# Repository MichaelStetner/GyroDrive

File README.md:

# GyroDrive
Motorized microdrive with integrated gyroscope, accelerometer, and compass

## Connector
The connector is a 7-pin male nano dual row connector from Omnetics (part number A75243-001).

Here is the pinout solder pads, as viewed from above with the connector pins pointing up

```
|                                                                       |
|                              Connector                                |
|                                Body                                   |
|                                                                       |
|                                                                       |
|-----------------------------------------------------------------------|

  |------|  |------|  |------|  |------|  |------|  |------|  |------|
  |      |  |      |  |      |  |      |  |      |  |      |  |      |
  | SCL  |  | SDA  |  |  S1  |  |  S2  |  | +VS  |  | -VS  |  | STIM |
  |      |  |      |  |      |  |      |  |      |  |      |  | OUT  |
  |      |  |      |  |      |  |      |  |      |  |      |  |      |
  |------|  |------|  |------|  |------|  |------|  |------|  |------|

  |------|  |------|  |------|  |------|  |------|  |------|  |------|
  |      |  |      |  |      |  |      |  |      |  |      |  |      |
  | DGND |  |  IX  |  |  S3  |  |  S4  |  | ICOM |  | AGND |  | STIM |
  |      |  |      |  |      |  |      |  |      |  |      |  |  IN  |
  |      |  |      |  |      |  |      |  |      |  |      |  |      |
  |------|  |------|  |------|  |------|  |------|  |------|  |------|
```

Here is the same pinout for the connector pins, as viewed looking head on into the pins with the board on the bottom

```
   /                                                                /
  /                                                                /
 /                                                                /
|----------------------------------------------------------------|
| |------| |------| |------| |------| |------| |------| |------| |
| | STIM | | AGND | | ICOM | |  S4  | |  S3  | |  IX  | | DGND | |
| |  IN  | |      | |      | |      | |      | |      | |      | |
| |------| |------| |------| |------| |------| |------| |------| |
|                                                                |    
| |------| |------| |------| |------| |------| |------| |------| |
| | STIM | | -VS  | | +VS  | |  S2  | |  S1  | | SDA  | | SCL  | |
| | OUT  | |      | |      | |      | |      | |      | |      | |  /
| |------| |------| |------| |------| |------| |------| |------| | /
|----------------------------------------------------------------|/
                            Board side
```

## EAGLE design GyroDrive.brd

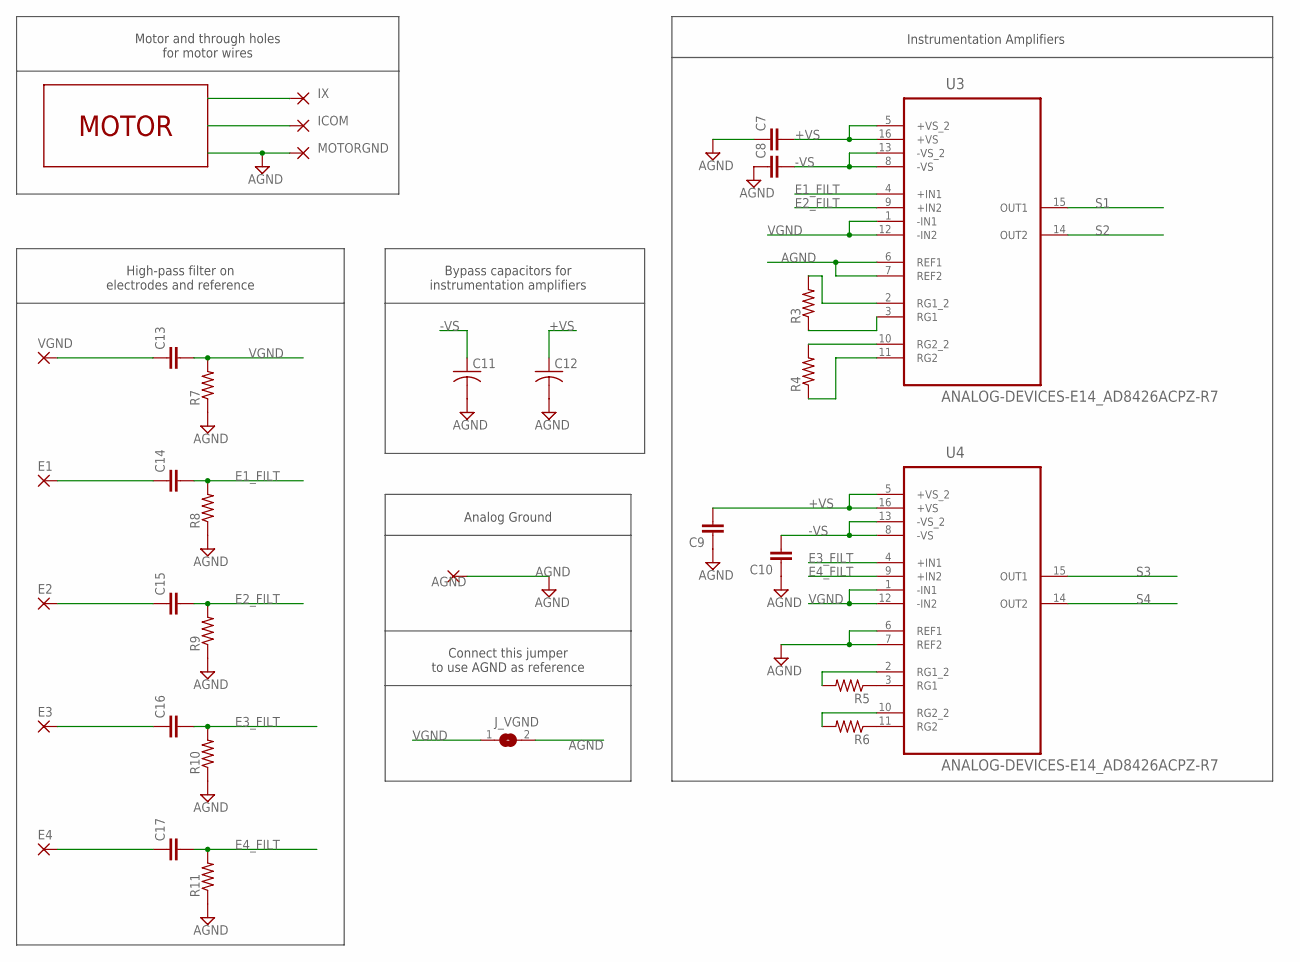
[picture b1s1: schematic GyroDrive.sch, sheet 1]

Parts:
AGND: THROUGH-HOLE-30MIL/15MIL; 30MIL/15MIL
C7, C8, C9, C10, C13, C14, C15, C16, C17: C-EUC0201; C0201
C11, C12: C-USC0603; C0603
E1, E2, E3, E4: SMD25-25-MIL
ICOM: THROUGH-HOLE-30MIL/15MIL; 30MIL/15MIL
IX: THROUGH-HOLE-30MIL/15MIL; 30MIL/15MIL
J_VGND: SJ
MOTORGND: THROUGH-HOLE-30MIL/15MIL; 30MIL/15MIL
R3, R4, R5, R6, R7, R8, R9, R10, R11: R-US_R0201; R0201
U3, U4: ANALOG-DEVICES-E14_AD8426ACPZ-R7; ANALOG-DEVICES-E14_QFN65P400X400X100-16N
U$2: MICRODRIVE-MOTOR; 0206A001B-021-47:1-Y2825
VGND: SMD25-25-MIL

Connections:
+VS: C7.2, C9.2, C12.1, U3.5 (+VS_2), U3.16 (+VS), U4.5 (+VS_2), U4.16 (+VS)
-VS: C8.2, C10.2, C11.1, U3.8 (-VS), U3.13 (-VS_2), U4.8 (-VS), U4.13 (-VS_2)
AGND: AGND.P$1, C7.1, C8.1, C9.1, C10.1, C11.2, C12.2, J_VGND.2, MOTORGND.P$1, R7.1, R8.1, R9.1, R10.1, R11.1, U3.6 (REF1), U3.7 (REF2), U4.6 (REF1), U4.7 (REF2)
E1: C14.1, E1.1
E1_FILT: C14.2, R8.2, U3.4 (+IN1)
E2: C15.1, E2.1
E2_FILT: C15.2, R9.2, U3.9 (+IN2)
E3: C16.1, E3.1
E3_FILT: C16.2, R10.2, U4.4 (+IN1)
E4: C17.1, E4.1
E4_FILT: C17.2, R11.2, U4.9 (+IN2)
ICOM: ICOM.P$1
IX: IX.P$1
unnamed: R4.2, U3.10 (RG2_2)
unnamed: R4.1, U3.11 (RG2)
unnamed: R3.1, U3.3 (RG1)
unnamed: R3.2, U3.2 (RG1_2)
unnamed: R5.1, U4.3 (RG1)
unnamed: R5.2, U4.2 (RG1_2)
unnamed: R6.2, U4.10 (RG2_2)
unnamed: R6.1, U4.11 (RG2)
S1: U3.15 (OUT1)
S2: U3.14 (OUT2)
S3: U4.15 (OUT1)
S4: U4.14 (OUT2)
VGND: C13.2, J_VGND.1, R7.2, U3.1 (-IN1), U3.12 (-IN2), U4.1 (-IN1), U4.12 (-IN2)
VGND_IN: C13.1

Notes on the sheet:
Bypass capacitors for instrumentation amplifiers
Connect this jumper to use AGND as reference
High-pass filter on electrodes and reference
Motor and through holes for motor wires
Analog Ground
Instrumentation Amplifiers

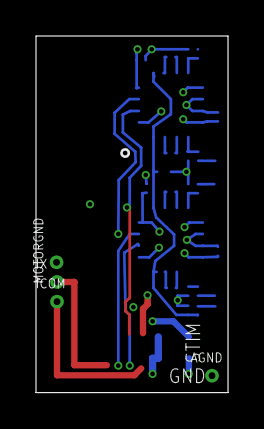
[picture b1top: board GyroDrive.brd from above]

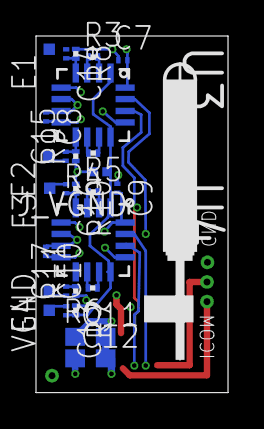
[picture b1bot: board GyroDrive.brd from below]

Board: 4 copper layers, 10.7 x 19.8 mm, 33 parts (29 on the bottom side), 20 nets.

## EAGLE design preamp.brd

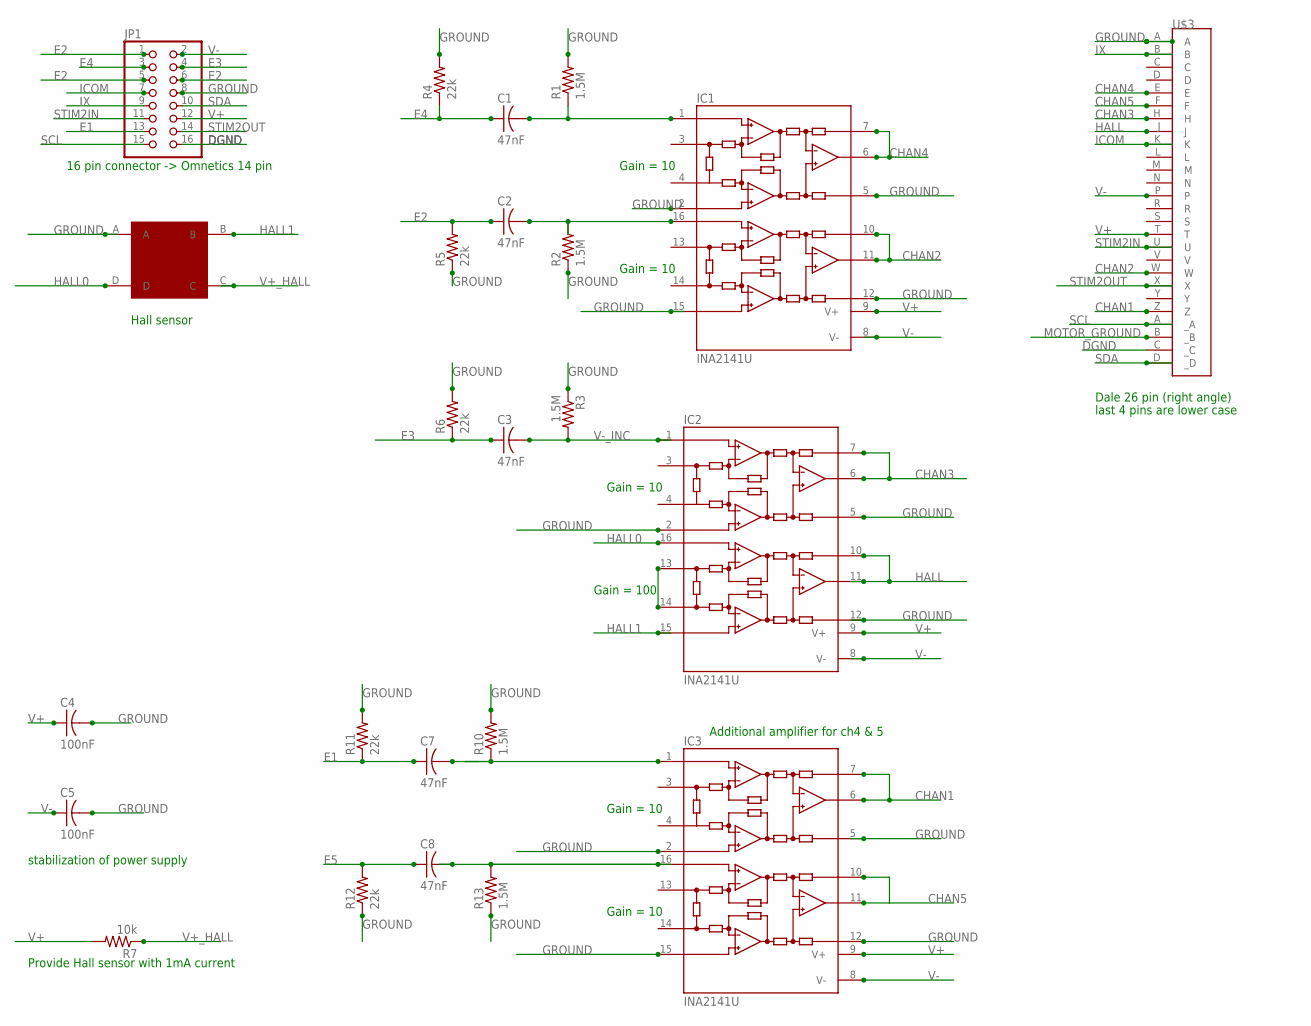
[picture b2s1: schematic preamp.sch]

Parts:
C1, C2, C3, C7, C8: 47nF; R0805ELM
C4, C5: 100nF; R0805ELM
IC1, IC2, IC3: INA2141U; SO16-1
JP1: PINHD-2X8; 2X08
R1, R2, R3, R10, R13: 1.5M; R0805ELM
R4, R5, R6, R11, R12: 22k; R0805ELM
R7: 10k; R0805ELM
U$2: HALL; HALL_ON_SIDE
U$3: MMD1P22G-26-M101

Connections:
CHAN1: IC3.6 (VOA), IC3.7 (SENSEA), U$3.Z
CHAN2: IC1.10 (SENSEB), IC1.11 (VOB), U$3.W
CHAN3: IC2.6 (VOA), IC2.7 (SENSEA), U$3.H
CHAN4: IC1.6 (VOA), IC1.7 (SENSEA), U$3.E
CHAN5: IC3.10 (SENSEB), IC3.11 (VOB), U$3.F
DGND: JP1.16, U$3._C
E1: C7.1, JP1.13, R11.1
E2: C2.1, JP1.1, JP1.5, JP1.6, R5.2
E3: C3.1, JP1.4, R6.1
E4: C1.1, JP1.3, R4.1
E5: C8.1, R12.2
GAIN_HALL: IC2.13 (JB), IC2.14 (JB)
GROUND: C4.2, C5.2, IC1.2 (INA+), IC1.5 (REFA), IC1.12 (REFB), IC1.15 (INB+), IC2.2 (INA+), IC2.5 (REFA), IC2.12 (REFB), IC3.2 (INA+), IC3.5 (REFA), IC3.12 (REFB), IC3.15 (INB+), JP1.8, R1.2, R2.1, R3.1, R4.2, R5.1, R6.2, R10.2, R11.2, R12.1, R13.1, U$2.A, U$3.A
HALL: IC2.10 (SENSEB), IC2.11 (VOB), U$3.J
HALL0: IC2.16 (INB-), U$2.D
HALL1: IC2.15 (INB+), U$2.B
ICOM: JP1.7, U$3.K
IX: JP1.9, U$3.B
MOTOR_GROUND: U$3._B
unnamed: C2.2, IC1.16 (INB-), R2.2
unnamed: C8.2, IC3.16 (INB-), R13.2
unnamed: C7.2, IC3.1 (INA-), R10.1
SCL: JP1.15, U$3._A
SDA: JP1.10, U$3._D
STIM2IN: JP1.11, U$3.U
STIM2OUT: JP1.14, U$3.X
V+: C4.1, IC1.9 (V+), IC2.9 (V+), IC3.9 (V+), JP1.12, R7.2, U$3.T
V+_HALL: R7.1, U$2.C
V-: C5.1, IC1.8 (V-), IC2.8 (V-), IC3.8 (V-), JP1.2, U$3.P
V-_INA: C1.2, IC1.1 (INA-), R1.1
V-_INC: C3.2, IC2.1 (INA-), R3.2

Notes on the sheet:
stabilization of power supply
Dale 26 pin (right angle)
Hall sensor
Additional amplifier for ch4 & 5
Gain = 100
Gain = 10
Provide Hall sensor with 1mA current
last 4 pins are lower case
16 pin connector -> Omnetics 14 pin

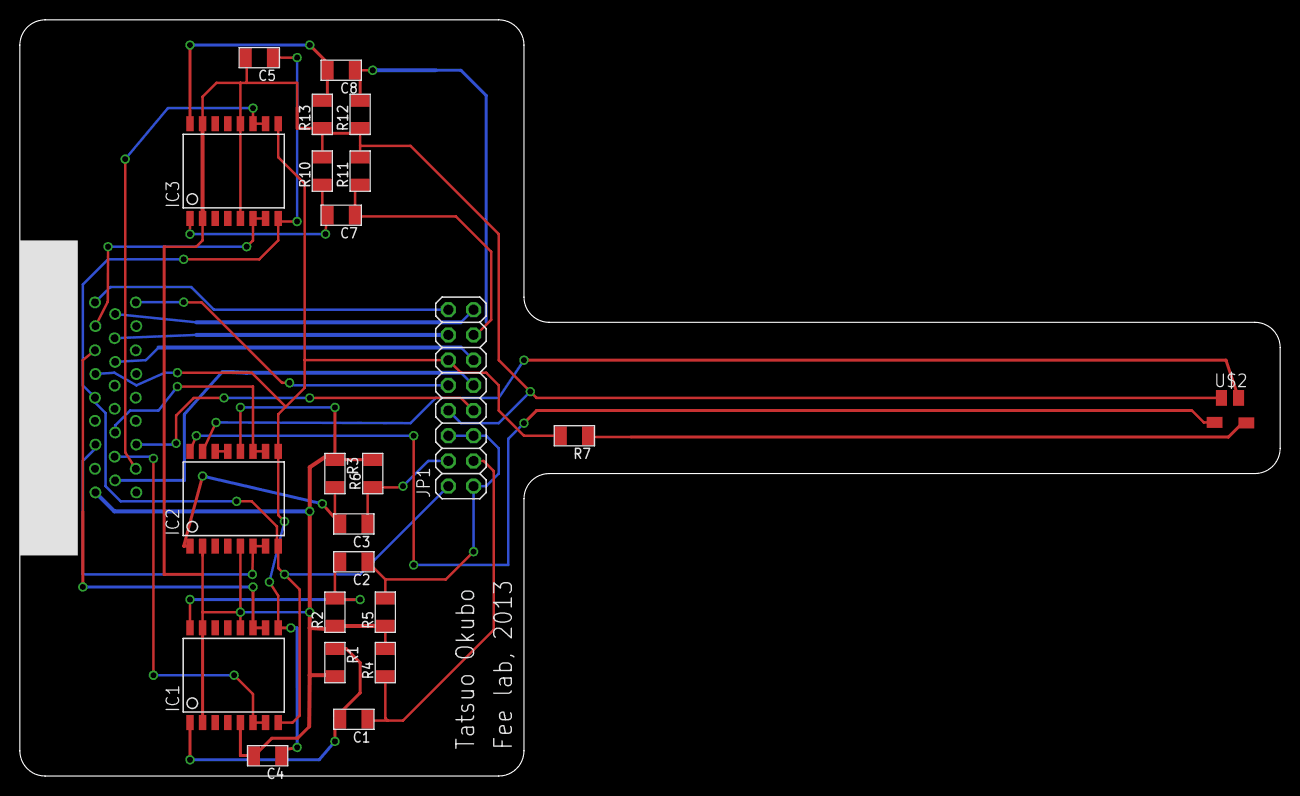
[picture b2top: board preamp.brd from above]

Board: 2 copper layers, 127.0 x 76.2 mm, 24 parts (0 on the bottom side), 30 nets.

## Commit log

2015-11-18 Schematic added, based on MicroIMU
2015-11-19 Preliminary board layout
2015-11-19 Preliminary layout with smaller through-holes
2015-11-19 Routing in progress. Having trouble with getting electrodes to FETs
2015-11-19 Routing in progress. FETs done, except VGND. Still need to rout stim and motor.
2015-11-20 Routing done
2015-11-20 In progress - rearrangement to put Omnetics connector lower, per Michale's suggestion
2015-12-01 Routing finished
2015-12-01 parts list spreadsheet added
2015-12-01 Cleaned up routing
2015-12-01 Added solder jumpers for SDA, SCL, and digital ground
2015-12-01 Moved SCL jumper to left of omnetics connector, separated motor ground from ground plane
2015-12-01 Bypass capacitor for L3GD20H rewired with more direct connection to 0V supply
2015-12-02 Silkscreen
2015-12-02 Silkscreen - added axes labels for gyroscope/accelerometer/magnetometer and also my name, lab, and year
2015-12-02 Rev 2 submitted to Advanced Circuits for quote. Fixed spacing issues.
2015-12-03 Changed schematic to make more sense (Rev 3 to Advanced Circuits)
    - Changed input voltage net name from +15V to VCC because VCC can be anything from 2.5V to 30V
    - Separate nets for digital and analog grounds (DGND and GND)
    -- Causes DRC to catch my mistake when digital and analog ground overlap
    - New nets SDAOUT and SCLOUT to represent SDA and SCL after passing through jumper
    -- Stops ratsnest from telling me I have things to do when the two terminals of the jumper are not connected to each other
    -- Pullup resistors moved to SDA and SCL nets (they used to be near omnetics connector on schematic, which put them on SDAOUT and SCLOUT)
2015-12-03 Corrected parts list - one of the 0.01 uF capacitors is 0402 size
2015-12-03 WIP: reroute with no vias or traces under chip
2016-01-13 Corrected capacitors in parts list
2016-01-15 Switched to Invensense MPU-9250
2016-01-15 Moved motor solder points lower
2016-01-26 Added instrumentation amplifiers for neural signals
2016-01-26 Removed copper from underneath MPU-9250
2016-01-26 Added jumper between VGND and AGND
2016-01-26 Moved vias to make return paths shorter
2016-01-26 Added attachment points for a grounding shield
2016-01-26 Made board more vertical - moved IMU up, and rotated instrumentation amplifier block by 90 degrees
2016-01-27 routing in progress
2016-01-27 Added pinout to readme
2016-01-27 Fixed formatting pinout table in ready
2016-01-27 Finished routing digital components
2016-01-28 Changed pinout, spaced vias for in-amps to minimum distance that avoids errors
2016-01-28 Cleaned up routing around in-amps
2016-01-28 Switched +VS and -VS on pinout and analog power layer. Finished routing!
2016-01-28 Added bypass capacitor for SDA pull-up resistor, shorted SDA and SCL jumpers with traces
2016-01-28 Changed pinout to group digital signals closer together
2016-01-29 Added high pass filters in front of inputs to in-amps
2016-01-29 Added Tatsuo's preamp design. Needs to be modified.
2016-01-29 Preamp - Removed VGROUND
    SIGNAL_GROUND net changed to GROUND
    Removed filter circuitry for VGROUND
    Removed toggle switch between GROUND and FILTERED_VGND for
2016-01-29 Changed JP1 pinout to match drive
    Stim 1 In > DGND
    Stim 1 Out > SCL
    IX > IX
    E4 > SDA
    VGND > E3
    E5 > E1
2016-01-29 Fixed dale connector part to stop giving dimension errors
2016-01-29 Added high pass filter for VGND. Attachment point for AGND changed to through hole.
2016-02-02 New instrumentation amplifier - AD8224. Old amplifier had too low bandwidth.
2016-02-02 Removed resistor to ground before blocking capacitors
2016-02-02 Instrumentation amplifier changed to AD8224
2016-02-02 Incorporated many improvements from the inamp-vertical branch
2016-02-02 Improvements suggested by Galen
    - Moved via to get rid of overlap with trace
    - Cleaned up routing
    - Moved S2 via away from corner of amplifier chip
    - Widened power traces
2016-02-03 Added silk screen (layers 121 and 122)
2016-02-08 updated libraries - removed pad on bottom of mpu 9250
2016-02-09 Updated parts list - added I2C pull up resistors (R10-R11)
2016-02-09 DISREGARD PREVIOUS COMMIT MESSAGE - nothing changed
2016-03-10 Updated .gitignore to ignore gerbers and eagleup files
2016-03-29 Updated parts list C4 changed to ceramic type (from tantalum) C13-C17 changed to 6800pF (from 47nF) R7-R11 changed to 10M (from 1.5M)
2016-04-25 Added motor holder drawing (SketchUp)
2016-04-27 updated motor holder
    - support for shuttle lowered by 150 um
    - support for shuttle widened by 50 um
2016-05-23 added design for motor holder
2018-12-30 formatted parts list for thesis
2018-12-30 digital schematic for thesis
2018-12-30 analog schematic for thesis
2018-12-31 remove redundant motor holder drawings
